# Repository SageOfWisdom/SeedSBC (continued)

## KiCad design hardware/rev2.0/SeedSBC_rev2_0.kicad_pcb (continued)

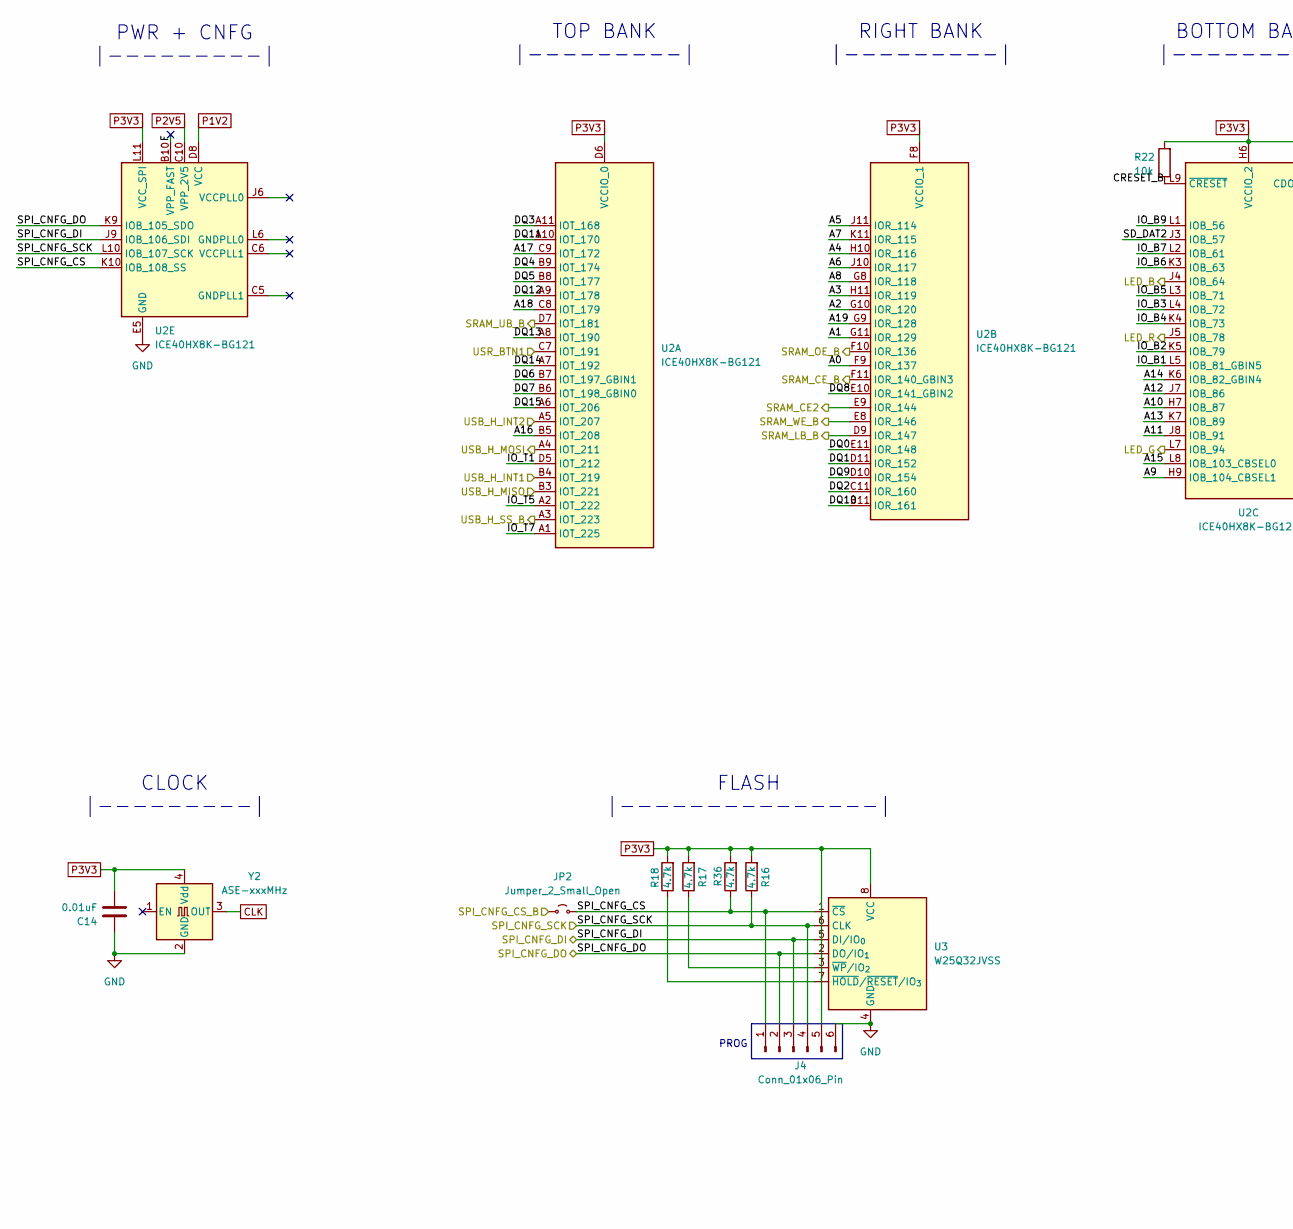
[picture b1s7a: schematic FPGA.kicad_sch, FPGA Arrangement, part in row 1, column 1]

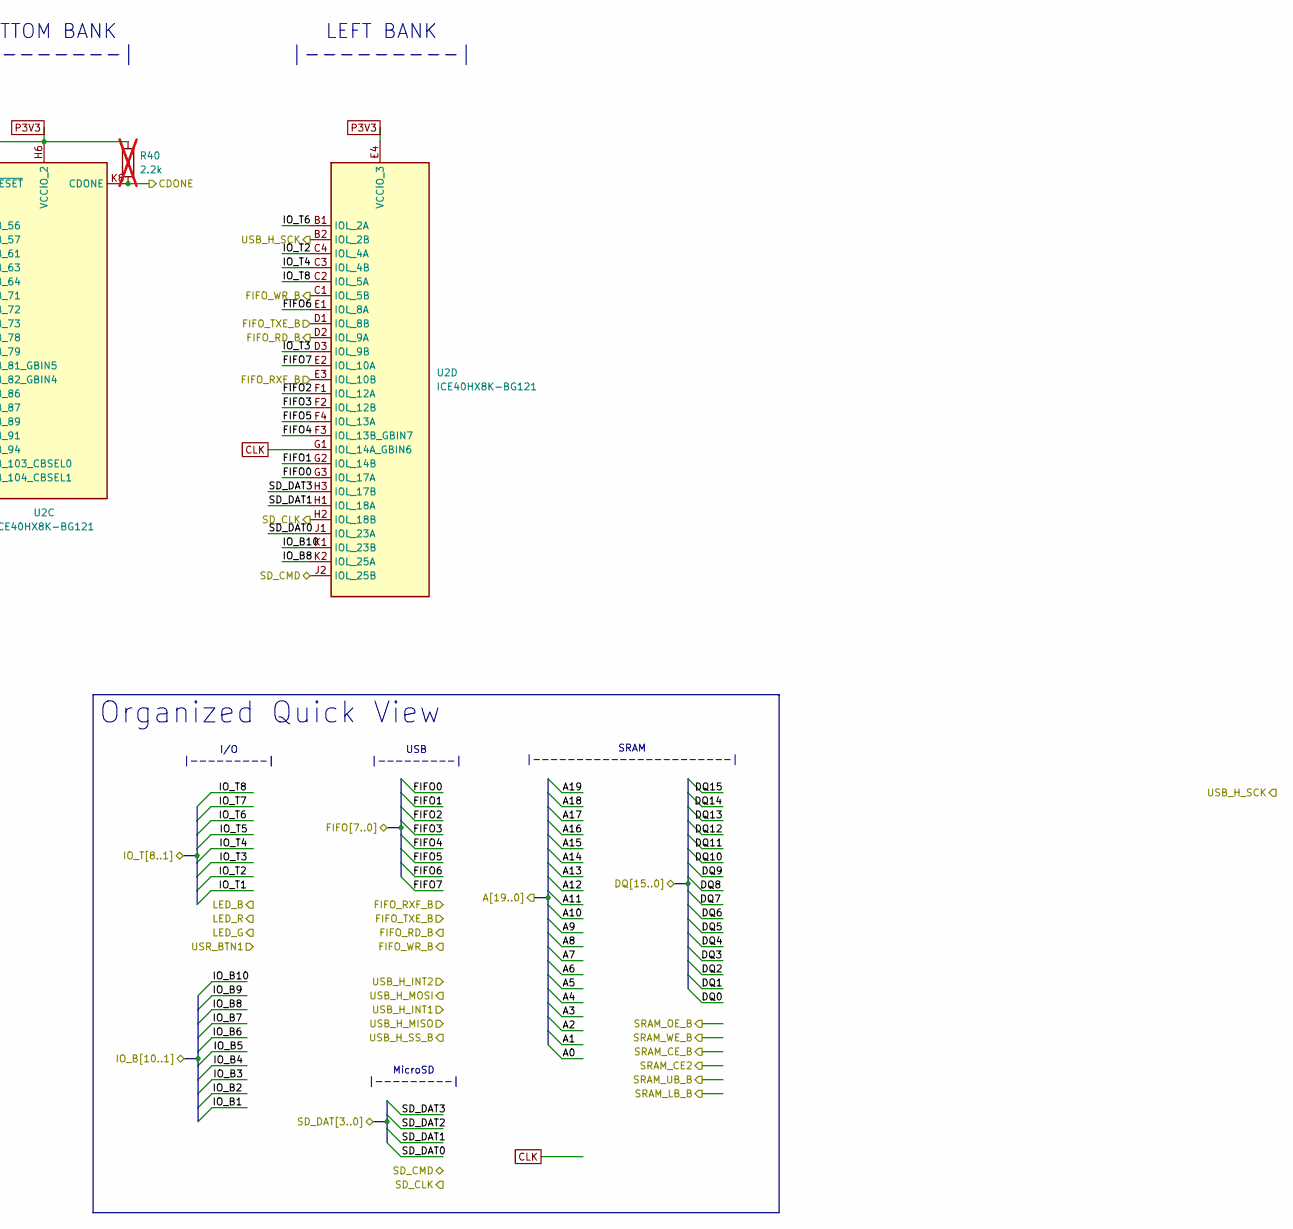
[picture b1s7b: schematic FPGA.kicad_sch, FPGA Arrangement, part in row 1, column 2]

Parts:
C14: 0.01uF; C_0603_1608Metric
J4: Conn_01x06_Pin; PinHeader_1x06_P2.54mm_Vertical
JP2: Jumper_2_Small_Open; SW_DIP_SPSTx01_Slide_6.7x4.1mm_W6.73mm_P2.54mm_LowProfile_J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
R16, R17, R18, R36: 4.7k; R_0603_1608Metric
R22: 10k; R_0603_1608Metric
R40: 2.2k; R_0603_1608Metric; not fitted
U2: ICE40HX8K-BG121; BGA-121_9.0x9.0mm_Layout11x11_P0.8mm_Ball0.4mm_Pad0.35mm_NS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
U3: W25Q32JVSS; SOIC-8_5.3x5.3mm_P1.27mm
Y2: ASE-xxxMHz; Oscillator_SMD_Abracon_ASE-4Pin_3.2x2.5mm

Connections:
/FPGA + SRAM/CDONE: R40.1, U2.K8 (CDONE); also elsewhere on the board
/FPGA + SRAM/FIFO0: U2.G3 (IOL_17A); also elsewhere on the board
/FPGA + SRAM/FIFO1: U2.G2 (IOL_14B); also elsewhere on the board
/FPGA + SRAM/FIFO2: U2.F1 (IOL_12A); also elsewhere on the board
/FPGA + SRAM/FIFO3: U2.F2 (IOL_12B); also elsewhere on the board
/FPGA + SRAM/FIFO4: U2.F3 (IOL_13B_GBIN7); also elsewhere on the board
/FPGA + SRAM/FIFO5: U2.F4 (IOL_13A); also elsewhere on the board
/FPGA + SRAM/FIFO6: U2.E1 (IOL_8A); also elsewhere on the board
/FPGA + SRAM/FIFO7: U2.E2 (IOL_10A); also elsewhere on the board
/FPGA + SRAM/FIFO_RD_B: U2.D2 (IOL_9A); also elsewhere on the board
/FPGA + SRAM/FIFO_RXF_B: U2.E3 (IOL_10B); also elsewhere on the board
/FPGA + SRAM/FIFO_TXE_B: U2.D1 (IOL_8B); also elsewhere on the board
/FPGA + SRAM/FIFO_WR_B: U2.C1 (IOL_5B); also elsewhere on the board
/FPGA + SRAM/FPGA/A0: U2.F9 (IOR_137); also elsewhere on the board
/FPGA + SRAM/FPGA/A1: U2.G11 (IOR_129); also elsewhere on the board
/FPGA + SRAM/FPGA/A2: U2.G10 (IOR_120); also elsewhere on the board
/FPGA + SRAM/FPGA/A3: U2.H11 (IOR_119); also elsewhere on the board
/FPGA + SRAM/FPGA/A4: U2.H10 (IOR_116); also elsewhere on the board
/FPGA + SRAM/FPGA/A5: U2.J11 (IOR_114); also elsewhere on the board
/FPGA + SRAM/FPGA/A6: U2.J10 (IOR_117); also elsewhere on the board
/FPGA + SRAM/FPGA/A7: U2.K11 (IOR_115); also elsewhere on the board
/FPGA + SRAM/FPGA/A8: U2.G8 (IOR_118); also elsewhere on the board
/FPGA + SRAM/FPGA/A9: U2.H9 (IOB_104_CBSEL1); also elsewhere on the board
/FPGA + SRAM/FPGA/A10: U2.H7 (IOB_87); also elsewhere on the board
/FPGA + SRAM/FPGA/A11: U2.J8 (IOB_91); also elsewhere on the board
/FPGA + SRAM/FPGA/A12: U2.J7 (IOB_86); also elsewhere on the board
/FPGA + SRAM/FPGA/A13: U2.K7 (IOB_89); also elsewhere on the board
/FPGA + SRAM/FPGA/A14: U2.K6 (IOB_82_GBIN4); also elsewhere on the board
/FPGA + SRAM/FPGA/A15: U2.L8 (IOB_103_CBSEL0); also elsewhere on the board
/FPGA + SRAM/FPGA/A16: U2.B5 (IOT_208); also elsewhere on the board
/FPGA + SRAM/FPGA/A17: U2.C9 (IOT_172); also elsewhere on the board
/FPGA + SRAM/FPGA/A18: U2.C8 (IOT_179); also elsewhere on the board
/FPGA + SRAM/FPGA/A19: U2.G9 (IOR_128); also elsewhere on the board
/FPGA + SRAM/FPGA/CRESET_B: R22.1, U2.L9 (~CRESET)
/FPGA + SRAM/FPGA/DQ0: U2.E11 (IOR_148); also elsewhere on the board
/FPGA + SRAM/FPGA/DQ1: U2.D11 (IOR_152); also elsewhere on the board
/FPGA + SRAM/FPGA/DQ2: U2.C11 (IOR_160); also elsewhere on the board
/FPGA + SRAM/FPGA/DQ3: U2.A11 (IOT_168); also elsewhere on the board
/FPGA + SRAM/FPGA/DQ4: U2.B9 (IOT_174); also elsewhere on the board
/FPGA + SRAM/FPGA/DQ5: U2.B8 (IOT_177); also elsewhere on the board
/FPGA + SRAM/FPGA/DQ6: U2.B7 (IOT_197_GBIN1); also elsewhere on the board
/FPGA + SRAM/FPGA/DQ7: U2.B6 (IOT_198_GBIN0); also elsewhere on the board
/FPGA + SRAM/FPGA/DQ8: U2.E10 (IOR_141_GBIN2); also elsewhere on the board
/FPGA + SRAM/FPGA/DQ9: U2.D10 (IOR_154); also elsewhere on the board
/FPGA + SRAM/FPGA/DQ10: U2.B11 (IOR_161); also elsewhere on the board
/FPGA + SRAM/FPGA/DQ11: U2.A10 (IOT_170); also elsewhere on the board
/FPGA + SRAM/FPGA/DQ12: U2.A9 (IOT_178); also elsewhere on the board
/FPGA + SRAM/FPGA/DQ13: U2.A8 (IOT_190); also elsewhere on the board
/FPGA + SRAM/FPGA/DQ14: U2.A7 (IOT_192); also elsewhere on the board
/FPGA + SRAM/FPGA/DQ15: U2.A6 (IOT_206); also elsewhere on the board
/FPGA + SRAM/FPGA/F: U2.B10 (VPP_FAST)
/FPGA + SRAM/FPGA/SPI_CNFG_CS: J4.1, JP2.2 (B), R36.1, U2.K10 (IOB_108_SS), U3.1 (~CS)
/FPGA + SRAM/FPGA/SPI_CNFG_DI: J4.3, U2.J9 (IOB_106_SDI), U3.5 (DI/IO_{0}); also elsewhere on the board
/FPGA + SRAM/FPGA/SPI_CNFG_DO: J4.2, U2.K9 (IOB_105_SDO), U3.2 (DO/IO_{1}); also elsewhere on the board
/FPGA + SRAM/FPGA/SPI_CNFG_SCK: J4.4, R16.1, U2.L10 (IOB_107_SCK), U3.6 (CLK); also elsewhere on the board
/FPGA + SRAM/FPGA/SRAM_CE2: U2.E9 (IOR_144); also elsewhere on the board
/FPGA + SRAM/FPGA/SRAM_CE_B: U2.F11 (IOR_140_GBIN3); also elsewhere on the board
/FPGA + SRAM/FPGA/SRAM_LB_B: U2.D9 (IOR_147); also elsewhere on the board
/FPGA + SRAM/FPGA/SRAM_OE_B: U2.F10 (IOR_136); also elsewhere on the board
/FPGA + SRAM/FPGA/SRAM_UB_B: U2.D7 (IOT_181); also elsewhere on the board
/FPGA + SRAM/FPGA/SRAM_WE_B: U2.E8 (IOR_146); also elsewhere on the board
/FPGA + SRAM/IO_B1: U2.L5 (IOB_81_GBIN5); also elsewhere on the board
/FPGA + SRAM/IO_B2: U2.K5 (IOB_79); also elsewhere on the board
/FPGA + SRAM/IO_B3: U2.L4 (IOB_72); also elsewhere on the board
/FPGA + SRAM/IO_B4: U2.K4 (IOB_73); also elsewhere on the board
/FPGA + SRAM/IO_B5: U2.L3 (IOB_71); also elsewhere on the board
/FPGA + SRAM/IO_B6: U2.K3 (IOB_63); also elsewhere on the board
/FPGA + SRAM/IO_B7: U2.L2 (IOB_61); also elsewhere on the board
/FPGA + SRAM/IO_B8: U2.K2 (IOL_25A); also elsewhere on the board
/FPGA + SRAM/IO_B9: U2.L1 (IOB_56); also elsewhere on the board
/FPGA + SRAM/IO_B10: U2.K1 (IOL_23B); also elsewhere on the board
/FPGA + SRAM/IO_T1: U2.D5 (IOT_212); also elsewhere on the board
/FPGA + SRAM/IO_T2: U2.C4 (IOL_4A); also elsewhere on the board
/FPGA + SRAM/IO_T3: U2.D3 (IOL_9B); also elsewhere on the board
/FPGA + SRAM/IO_T4: U2.C3 (IOL_4B); also elsewhere on the board
/FPGA + SRAM/IO_T5: U2.A2 (IOT_222); also elsewhere on the board
/FPGA + SRAM/IO_T6: U2.B1 (IOL_2A); also elsewhere on the board
/FPGA + SRAM/IO_T7: U2.A1 (IOT_225); also elsewhere on the board
/FPGA + SRAM/IO_T8: U2.C2 (IOL_5A); also elsewhere on the board
/FPGA + SRAM/LED_B: U2.J4 (IOB_64); also elsewhere on the board
/FPGA + SRAM/LED_G: U2.L7 (IOB_94); also elsewhere on the board
/FPGA + SRAM/LED_R: U2.J5 (IOB_78); also elsewhere on the board
/FPGA + SRAM/SD_CLK: U2.H2 (IOL_18B); also elsewhere on the board
/FPGA + SRAM/SD_DAT0: U2.J1 (IOL_23A); also elsewhere on the board
/FPGA + SRAM/SD_DAT1: U2.H1 (IOL_18A); also elsewhere on the board
/FPGA + SRAM/SD_DAT2: U2.J3 (IOB_57); also elsewhere on the board
/FPGA + SRAM/SD_DAT3: U2.H3 (IOL_17B); also elsewhere on the board
/FPGA + SRAM/SPI_CNFG_CS_B: JP2.1 (A); also elsewhere on the board
/FPGA + SRAM/USB_H_INT1: U2.B4 (IOT_219); also elsewhere on the board
/FPGA + SRAM/USB_H_INT2: U2.A5 (IOT_207); also elsewhere on the board
/FPGA + SRAM/USB_H_MISO: U2.B3 (IOT_221); also elsewhere on the board
/FPGA + SRAM/USB_H_MOSI: U2.A4 (IOT_211); also elsewhere on the board
/FPGA + SRAM/USB_H_SCK: U2.B2 (IOL_2B); also elsewhere on the board
/FPGA + SRAM/USB_H_SS_B: U2.A3 (IOT_223); also elsewhere on the board
/FPGA + SRAM/USR_BTN1: U2.C7 (IOT_191); also elsewhere on the board
/SD MMC/SD_CMD: U2.J2 (IOL_25B); also elsewhere on the board
CLK: U2.G1 (IOL_14A_GBIN6), Y2.3 (OUT)
GND: C14.2, J4.6, U2.E5 (GND), U2.E6 (GND), U2.E7 (GND), U2.F5 (GND), U2.F6 (GND), U2.F7 (GND), U2.G5 (GND), U2.G6 (GND), U2.G7 (GND), U2.H5 (GND), U3.4 (GND), Y2.2 (GND); also elsewhere on the board
unnamed: R18.1, U3.7 (~HOLD/~RESET/IO_{3})
unnamed: R17.1, U3.3 (~WP/IO_{2})
P1V2: U2.D4 (VCC), U2.D8 (VCC), U2.H4 (VCC), U2.H8 (VCC); also elsewhere on the board
P2V5: U2.C10 (VPP_2V5); also elsewhere on the board

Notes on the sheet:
LEFT BANK |---------|
TOP BANK |---------|
SRAM |-----------------------|
I/O |---------|
USB |---------|
BOTTOM BANK |---------|
PROG
FLASH |---------------|
CLOCK |---------|
RIGHT BANK |---------|
PWR + CNFG |---------|
MicroSD |---------|
Organized Quick View

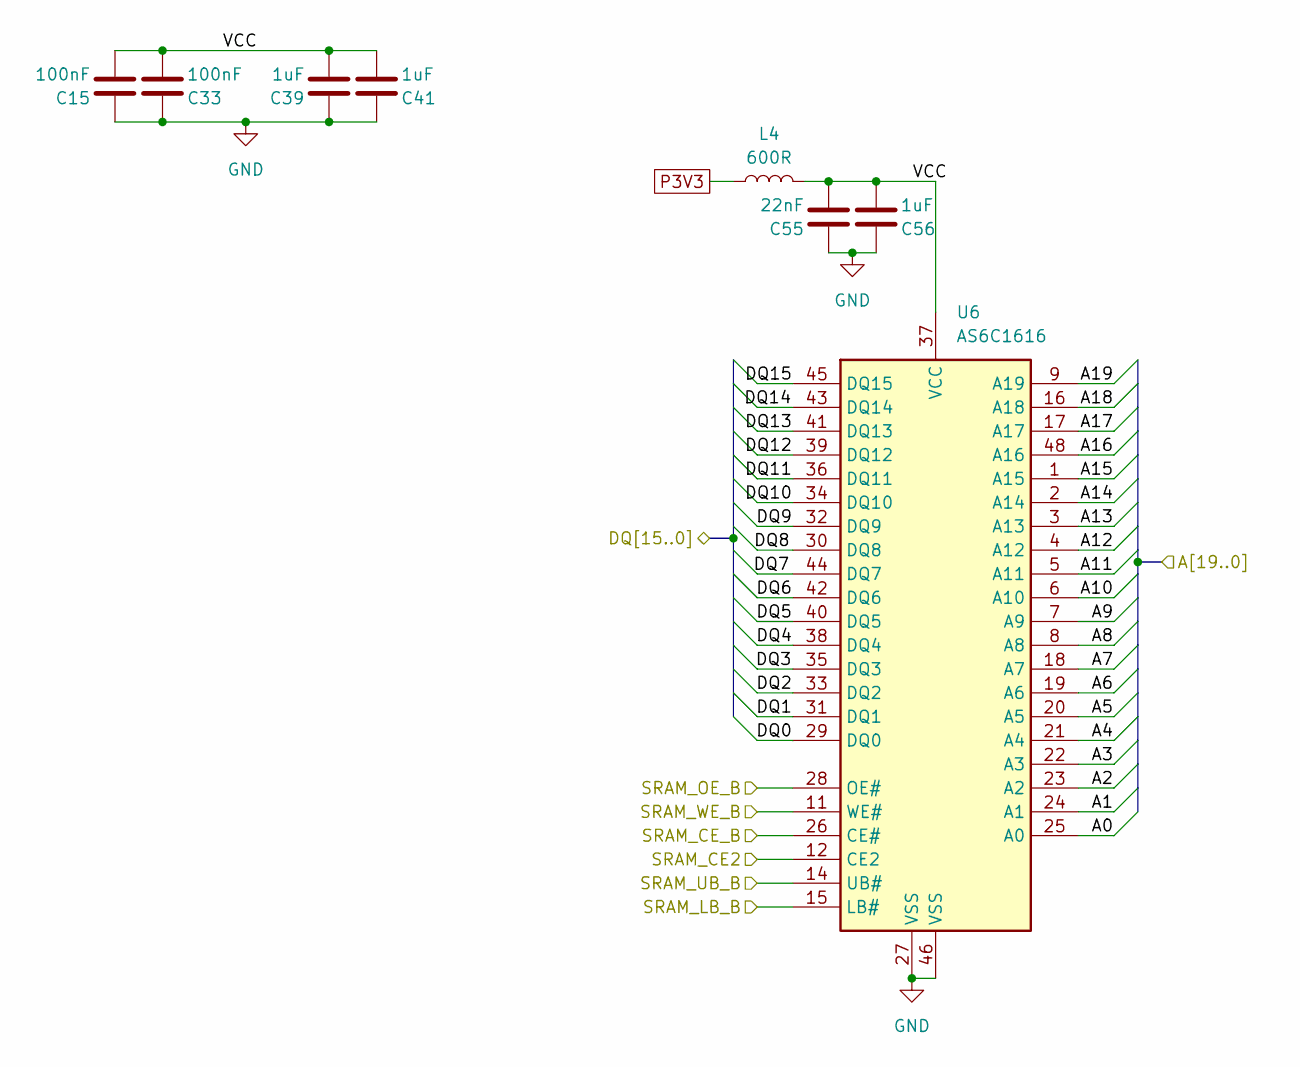
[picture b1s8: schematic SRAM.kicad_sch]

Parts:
C15, C33: 100nF
C39, C41, C56: 1uF
C55: 22nF
L4: 600R
U6: AS6C1616; TSOP-I-48_18.4x12mm_P0.5mm

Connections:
/FPGA + SRAM/FPGA/A0: U6.25 (A0); also elsewhere on the board
/FPGA + SRAM/FPGA/A1: U6.24 (A1); also elsewhere on the board
/FPGA + SRAM/FPGA/A2: U6.23 (A2); also elsewhere on the board
/FPGA + SRAM/FPGA/A3: U6.22 (A3); also elsewhere on the board
/FPGA + SRAM/FPGA/A4: U6.21 (A4); also elsewhere on the board
/FPGA + SRAM/FPGA/A5: U6.20 (A5); also elsewhere on the board
/FPGA + SRAM/FPGA/A6: U6.19 (A6); also elsewhere on the board
/FPGA + SRAM/FPGA/A7: U6.18 (A7); also elsewhere on the board
/FPGA + SRAM/FPGA/A8: U6.8 (A8); also elsewhere on the board
/FPGA + SRAM/FPGA/A9: U6.7 (A9); also elsewhere on the board
/FPGA + SRAM/FPGA/A10: U6.6 (A10); also elsewhere on the board
/FPGA + SRAM/FPGA/A11: U6.5 (A11); also elsewhere on the board
/FPGA + SRAM/FPGA/A12: U6.4 (A12); also elsewhere on the board
/FPGA + SRAM/FPGA/A13: U6.3 (A13); also elsewhere on the board
/FPGA + SRAM/FPGA/A14: U6.2 (A14); also elsewhere on the board
/FPGA + SRAM/FPGA/A15: U6.1 (A15); also elsewhere on the board
/FPGA + SRAM/FPGA/A16: U6.48 (A16); also elsewhere on the board
/FPGA + SRAM/FPGA/A17: U6.17 (A17); also elsewhere on the board
/FPGA + SRAM/FPGA/A18: U6.16 (A18); also elsewhere on the board
/FPGA + SRAM/FPGA/A19: U6.9 (A19); also elsewhere on the board
/FPGA + SRAM/FPGA/DQ0: U6.29 (DQ0); also elsewhere on the board
/FPGA + SRAM/FPGA/DQ1: U6.31 (DQ1); also elsewhere on the board
/FPGA + SRAM/FPGA/DQ2: U6.33 (DQ2); also elsewhere on the board
/FPGA + SRAM/FPGA/DQ3: U6.35 (DQ3); also elsewhere on the board
/FPGA + SRAM/FPGA/DQ4: U6.38 (DQ4); also elsewhere on the board
/FPGA + SRAM/FPGA/DQ5: U6.40 (DQ5); also elsewhere on the board
/FPGA + SRAM/FPGA/DQ6: U6.42 (DQ6); also elsewhere on the board
/FPGA + SRAM/FPGA/DQ7: U6.44 (DQ7); also elsewhere on the board
/FPGA + SRAM/FPGA/DQ8: U6.30 (DQ8); also elsewhere on the board
/FPGA + SRAM/FPGA/DQ9: U6.32 (DQ9); also elsewhere on the board
/FPGA + SRAM/FPGA/DQ10: U6.34 (DQ10); also elsewhere on the board
/FPGA + SRAM/FPGA/DQ11: U6.36 (DQ11); also elsewhere on the board
/FPGA + SRAM/FPGA/DQ12: U6.39 (DQ12); also elsewhere on the board
/FPGA + SRAM/FPGA/DQ13: U6.41 (DQ13); also elsewhere on the board
/FPGA + SRAM/FPGA/DQ14: U6.43 (DQ14); also elsewhere on the board
/FPGA + SRAM/FPGA/DQ15: U6.45 (DQ15); also elsewhere on the board
/FPGA + SRAM/FPGA/SRAM_CE2: U6.12 (CE2); also elsewhere on the board
/FPGA + SRAM/FPGA/SRAM_CE_B: U6.26 (CE#); also elsewhere on the board
/FPGA + SRAM/FPGA/SRAM_LB_B: U6.15 (LB#); also elsewhere on the board
/FPGA + SRAM/FPGA/SRAM_OE_B: U6.28 (OE#); also elsewhere on the board
/FPGA + SRAM/FPGA/SRAM_UB_B: U6.14 (UB#); also elsewhere on the board
/FPGA + SRAM/FPGA/SRAM_WE_B: U6.11 (WE#); also elsewhere on the board
/FPGA + SRAM/SRAM/VCC: C15.1, C33.1, C39.1, C41.1, C55.1, C56.1, L4.2, U6.37 (VCC)
GND: C15.2, C33.2, C39.2, C41.2, C55.2, C56.2, U6.27 (VSS), U6.46 (VSS); also elsewhere on the board

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
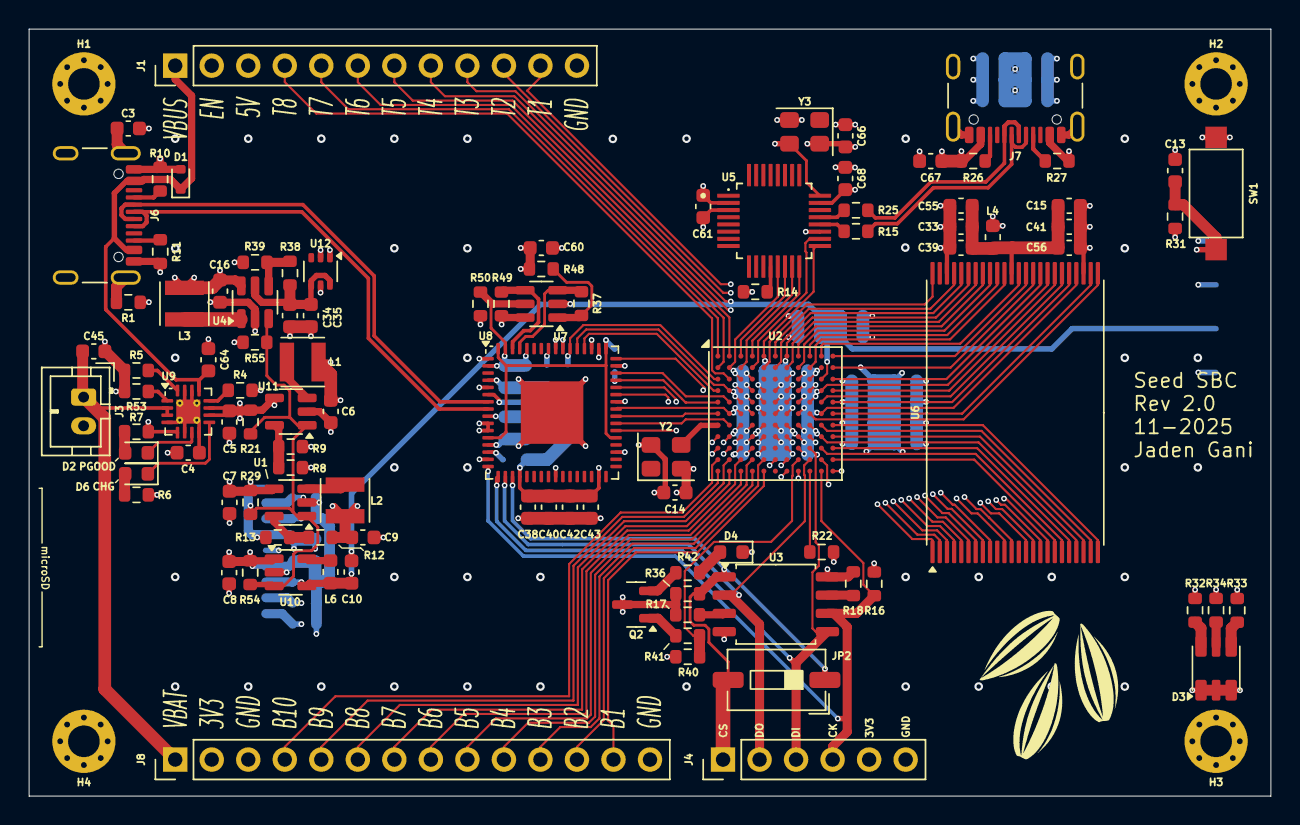
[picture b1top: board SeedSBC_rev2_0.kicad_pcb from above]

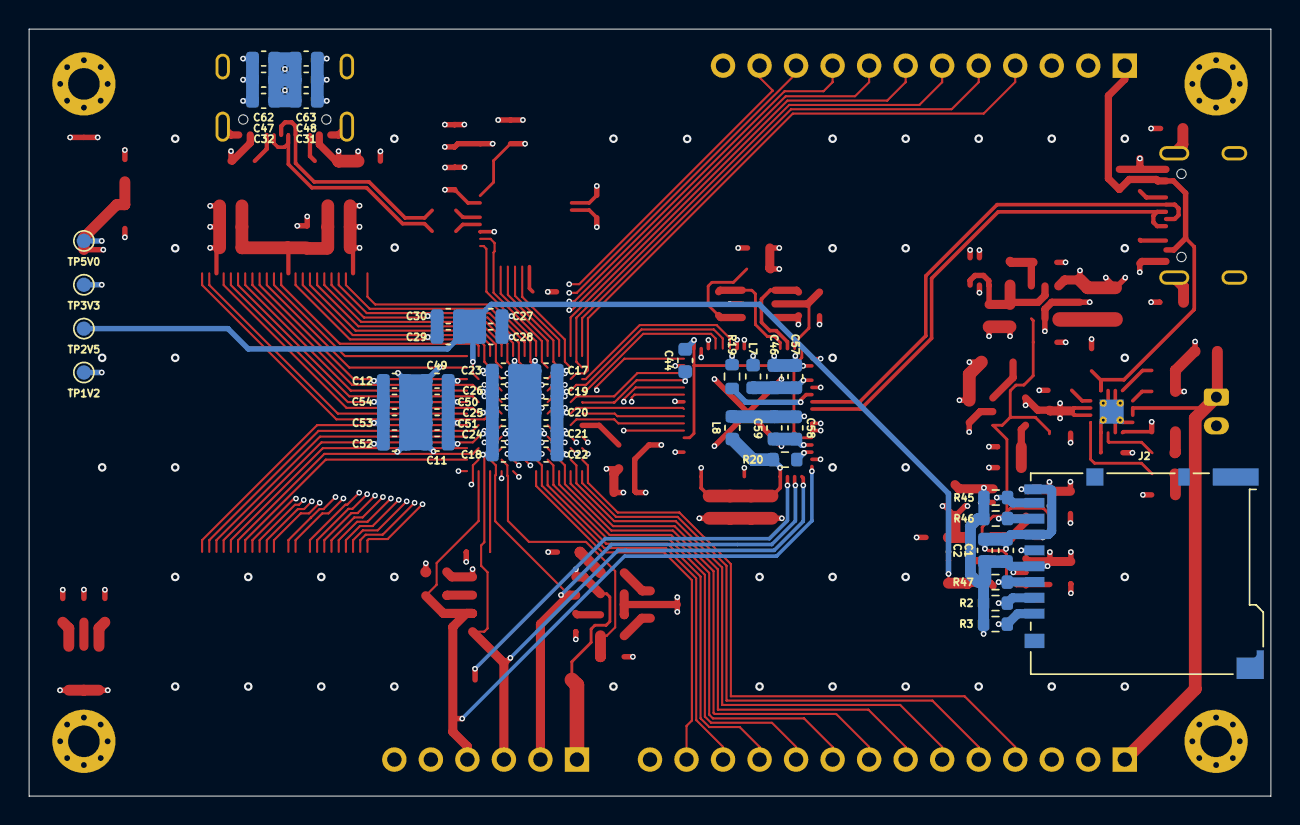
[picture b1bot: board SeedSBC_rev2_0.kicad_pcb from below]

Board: 8 copper layers, 86.4 x 53.3 mm, 156 parts (49 on the bottom side), 151 nets.

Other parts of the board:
C11: 100nF; C_0603_1608Metric
C12: 10nF; C_0603_1608Metric
C62, C63: 2.2uF; C_0603_1608Metric

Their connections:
GND: C11.2, C12.2, C62.2, C63.2; also elsewhere on the board
